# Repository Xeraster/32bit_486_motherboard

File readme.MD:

here are the schematics for the 32 bit 486 motherboard. This is the version where I fixed all the stuff that was wrong.

You will need the dual fpga chipset verilog code to run this. https://github.com/Xeraster/dual-ice40-fpga-486-chipset

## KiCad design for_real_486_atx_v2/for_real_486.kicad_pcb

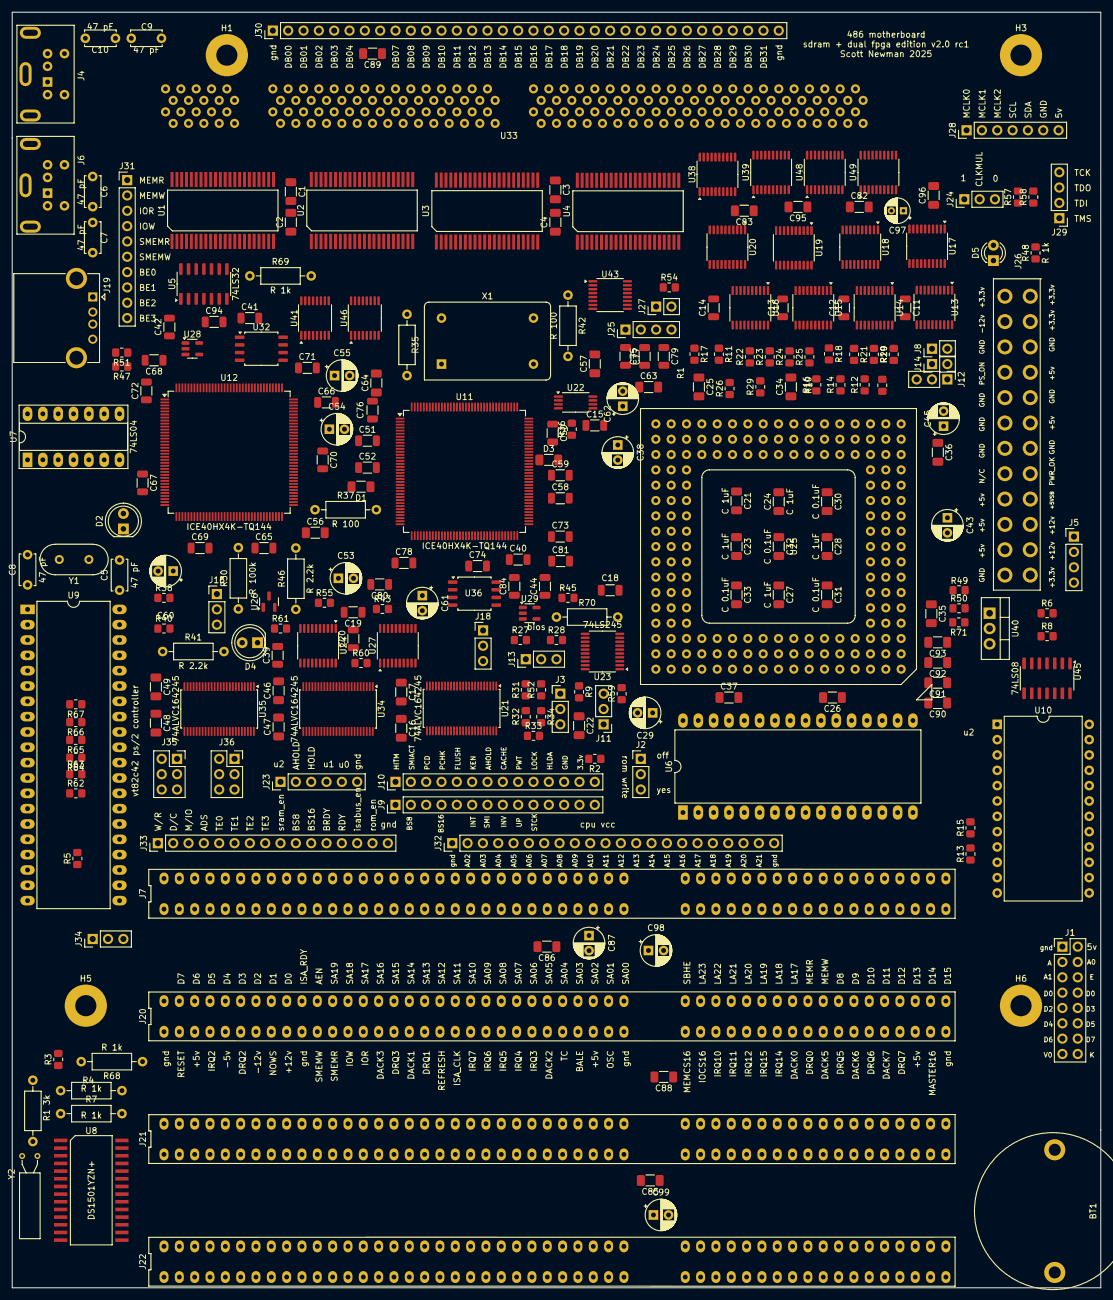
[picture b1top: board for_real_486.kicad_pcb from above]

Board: 4 copper layers, 180.3 x 211.3 mm, 256 parts (0 on the bottom side), 503 nets, no tracks yet.

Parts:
BT1: Battery_Cell; cr2032_holder
C1, C2, C3, C4, C30, C31, C32, C33, C34, C35, C36, C37, C56, C57, C64, C90, C92: C 0.1uF; C_1206_3216Metric_Pad1.33x1.80mm_HandSolder
C5, C6, C7, C8, C9, C10: 47 pF; C_Disc_D5.0mm_W2.5mm_P5.00mm
C11, C12, C13, C14, C18, C19, C20, C39, C40, C41, C42, C44, C65, C66, C69, C70, C73, C74, C77, C78, C81, C84, C94: C 0.1uF; C_1206_3216Metric
C15, C50: 0.1uF; C_1206_3216Metric
C16, C17, C46, C47, C48, C49, C82, C83, C85, C86, C95, C96: 0.1uF; C_1206_3216Metric_Pad1.33x1.80mm_HandSolder
C21, C22, C23, C24, C25, C26, C27, C28, C88, C89, C91, C93: C 1uF; C_1206_3216Metric_Pad1.33x1.80mm_HandSolder
C29, C38, C43, C45, C53, C54, C55, C60, C61, C62, C87, C98, C99: C_Polarized; CP_Radial_D5.0mm_P2.50mm
C51, C58: C 10uF; C_1206_3216Metric
C52, C59: SMD 0.1uF; C_1206_3216Metric
C63: C 0.1nF; C_1206_3216Metric_Pad1.33x1.80mm_HandSolder
C67, C68, C71, C72, C75, C76, C79, C80: C 1uF; C_1206_3216Metric
C97: C_Polarized; CP_Radial_D4.0mm_P2.00mm
D1, D3: D; C_1206_3216Metric_Pad1.33x1.80mm_HandSolder
D2, D4: LED; LED_D5.0mm
D5: LED; LED_D3.0mm
H1, H3, H5, H6: MountingHole; MountingHole_3.5mm_Pad
J1: Conn_02x08_Counter_Clockwise; PinHeader_2x08_P2.54mm_Vertical
J2, J3, J11, J12, J13, J16, J18, J24, J34: Conn_01x03; PinHeader_1x03_P2.54mm_Vertical
J4, J6: Mini-DIN-6; connector_mini6din
J5, J25, J29: Conn_01x04; PinHeader_1x04_P2.54mm_Vertical
J7, J20, J21, J22: Bus_ISA_16bit; DIP-98_ISA
J8, J14, J27: Conn_01x02; PinHeader_1x02_P2.54mm_Vertical
J9, J10: Conn_01x14; PinHeader_1x14_P2.54mm_Vertical
J19: USB_A; USB_A_CONNFLY_DS1095-WNR0
J23: Conn_01x06; PinHeader_1x06_P2.54mm_Vertical
J26: ATX-24; 24pinATX_newer
J28: Conn_01x07; PinHeader_1x07_P2.54mm_Vertical
J30: Conn_01x34; PinHeader_1x34_P2.54mm_Vertical
J31: Conn_01x10; PinHeader_1x10_P2.54mm_Vertical
J32: Conn_01x22; PinHeader_1x22_P2.54mm_Vertical
J33: Conn_01x16; PinHeader_1x16_P2.54mm_Vertical
J35, J36: Conn_01x06; PinSocket_2x03_P2.54mm_Vertical
R1: 3k; R_Axial_DIN0207_L6.3mm_D2.5mm_P10.16mm_Horizontal
R2, R3, R5, R9, R10, R11, R12, R14, R16, R26, R29, R31, R32, R33, R34, R38, R40, R43, R45, R52, R55, R57, R58, R59, R60, R61, R62, R63, R64, R65, R66, R67: R 10k; R_0805_2012Metric_Pad1.20x1.40mm_HandSolder
R4, R7, R35, R68, R69, R70: R 1k; R_Axial_DIN0207_L6.3mm_D2.5mm_P10.16mm_Horizontal
R6, R8, R48, R54: R 1k; R_0805_2012Metric_Pad1.20x1.40mm_HandSolder
R13, R15, R18, R19, R20, R21, R22, R23, R24, R25, R27, R28: 10k; R_0805_2012Metric_Pad1.20x1.40mm_HandSolder
R17: R 10K; R_0805_2012Metric_Pad1.20x1.40mm_HandSolder
R30: R 100k; R_Axial_DIN0207_L6.3mm_D2.5mm_P10.16mm_Horizontal
R36, R49, R50, R71: R; R_0805_2012Metric_Pad1.20x1.40mm_HandSolder
R37, R42: R 100; R_Axial_DIN0207_L6.3mm_D2.5mm_P10.16mm_Horizontal
R41, R46: R 2.2k; R_Axial_DIN0207_L6.3mm_D2.5mm_P10.16mm_Horizontal
R47, R51: R 33; R_0805_2012Metric_Pad1.20x1.40mm_HandSolder
U1, U2, U3, U4: CY7C1049G30; TSOP-44
U5: 74LS32; SO-14_3.9x8.65mm_P1.27mm
U6: 29F010-PDIP; DIP-32_W15.24mm_LongPads
U7: 74LS04; DIP-14_W7.62mm_Socket_LongPads
U8: DS1501YZN+; SOIC-BQ4845
U9: HT6542B; DIP-40_W15.24mm_LongPads
U10: 8254; DIP-24_W15.24mm
U11, U12: ICE40HX4K-TQ144; TQFP-144_20x20mm_P0.5mm
U13, U14, U15, U16, U17, U18, U19, U20, U23, U24, U27: 74LS245; TSSOP-20_4.4x6.5mm_P0.65mm
U21, U34, U35: 74ALVC164245; TSSOP-48_6.1x12.5mm_P0.5mm
U22: LMK1C1103PWR; TSSOP-8_4.4x3mm_P0.65mm
U25: i486SX; PGA168
U26: LM809; SOT-23
U28, U29: AP7347DQ; SOT-23-5
U32, U36: SOIC-8_5.275x5.275mm_P1.27mm
U33: SDRAM_socket
U38, U39, U48, U49: 74LS373; TSSOP-20_4.4x6.5mm_P0.65mm
U40: LM317_TO-220; TO-220-3_Vertical
U41, U43, U46: 74LS165; TSSOP-16_4.4x5mm_P0.65mm
U45: 74LS08; SO-14_3.9x8.65mm_P1.27mm
X1: ACO-xxxMHz-A; Oscillator_DIP-14
Y1: Crystal; Crystal_HC18-U_Vertical
Y2: Crystal; Crystal_AT310_D3.0mm_L10.0mm_Horizontal

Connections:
+1V2: C44.1, C53.1, C54.1, C60.1, C61.1, C69.1, C70.1, C71.1, C72.1, C77.1, C78.1, C79.1, C80.1, C94.1, R37.1, R42.1, U11.27 (VCC), U11.40 (VCC), U11.92 (VCC), U11.111 (VCC), U12.27 (VCC), U12.40 (VCC), U12.92 (VCC), U12.111 (VCC), U28.5 (V_out), U29.5 (V_out)
+3.3V: C1.1, C2.1, C3.1, C4.1, C11.2, C12.1, C13.1, C14.1, C15.2, C17.1, C18.2, C19.1, C20.1, C39.1, C40.1, C41.1, C42.1, C43.1, C47.1, C49.1, C50.1, C55.1, C56.2, C57.2, C62.1, C63.2, C64.2, C65.1, C66.1, C67.1, C68.1, C73.1, C74.1, C75.1, C76.1, C82.1, C83.1, C84.1, C85.1, C86.1, C87.1, C88.1, C89.1, C95.1, C96.1, C97.1, D1.2 (A), D3.2 (A), J10.13, J26.1 (+3.3V), J26.2 (+3.3V), J26.12 (+3.3V), J26.13 (+3.3V), J35.6, J36.6, R10.1, R12.1, R14.1, R16.1, R19.2, R20.1, R21.1, R36.2, R38.1, R40.2, R43.1, R45.2, R55.1, R59.1, R60.1, R61.1, R69.2, R70.2, U1.11 (VCC), U1.33 (VCC), U2.11 (VCC), U2.33 (VCC), U3.11 (VCC), U3.33 (VCC), U4.11 (VCC), U4.33 (VCC), U5.14 (VCC), U11.6 (VCCIO_3), U11.30 (VCCIO_3), U11.46 (VCCIO_2), U11.57 (VCCIO_2), U11.72 (VCC_SPI), U11.89 (VCCIO_1), U11.100 (VCCIO_1), U11.123 (VCCIO_0), U11.131 (VCCIO_0), U12.6 (VCCIO_3), U12.30 (VCCIO_3), U12.46 (VCCIO_2), U12.57 (VCCIO_2), U12.72 (VCC_SPI), U12.89 (VCCIO_1), U12.100 (VCCIO_1), U12.123 (VCCIO_0), U12.131 (VCCIO_0), U13.20 (VCC), U14.20 (VCC), U15.20 (VCC), U16.20 (VCC), U17.20 (VCC), U18.20 (VCC), U19.20 (VCC), U20.20 (VCC), U21.31 (V_{CC(A)}), U21.42 (V_{CC(A)}), U22.6 (VDD), U23.20 (VCC), U24.20 (VCC), U26.3 (VCC), U27.20 (VCC), U28.1 (V_in), U29.1 (V_in), U32.8 (VCC), U33.6 (Vcc), U33.18 (Vcc), U33.26 (Vcc), U33.40 (Vcc), U33.41 (Vcc), U33.49 (Vcc), U33.59 (Vcc), U33.73 (Vcc), U33.84 (Vcc), U33.90 (Vcc), U33.102 (Vcc), U33.110 (Vcc), U33.124 (Vcc), U33.133 (Vcc), U33.143 (Vcc), U33.157 (Vcc), U33.168 (Vcc), U34.31 (V_{CC(A)}), U34.42 (V_{CC(A)}), U35.31 (V_{CC(A)}), U35.42 (V_{CC(A)}), U36.8 (VCC), U38.20 (VCC), U39.20 (VCC), U41.16 (VCC), U43.16 (VCC), U45.14 (VCC), U46.16 (VCC), U48.20 (VCC), U49.20 (VCC), X1.14 (Vcc)
+5V: C16.2, C45.1, C46.2, C48.2, C98.1, C99.1, J1.2, J1.3, J4.4, J6.4, J7.3 (+5V), J7.29 (VCC), J7.78 (+5V), J8.1, J12.1, J19.1 (VBUS), J20.3 (+5V), J20.29 (VCC), J20.78 (+5V), J21.3 (+5V), J21.29 (VCC), J21.78 (+5V), J22.3 (+5V), J22.29 (VCC), J22.78 (+5V), J26.4 (+5V), J26.6 (+5V), J26.21 (+5V), J26.22 (+5V), J26.23 (+5V), J27.2, J28.7, R2.1, R3.1, R4.1, R5.2, R6.2, R7.2, R8.2, U6.32 (VCC), U7.14 (VCC), U8.28 (Vcc), U9.26 (TEST), U9.40 (Vdd), U10.24 (VCC), U21.7 (V_{CC(B)}), U21.18 (V_{CC(B)}), U34.7 (V_{CC(B)}), U34.18 (V_{CC(B)}), U35.7 (V_{CC(B)}), U35.18 (V_{CC(B)})
+12V: C90.1, C91.1, J7.9 (+12V), J20.9 (+12V), J21.9 (+12V), J22.9 (+12V), J26.10 (+12V), J26.11 (+12V), U40.3 (VI)
A00: U11.41 (IOB_63), U13.2 (A0)
A01: U11.42 (IOB_64), U13.3 (A1)
A02: U13.4 (A2), U25.Q14 (A2)
A03: U13.5 (A3), U25.R15 (A3)
A04: U13.6 (A4), U25.S16 (A4)
A05: U13.7 (A5), U25.Q12 (A5)
A06: U13.8 (A6), U25.S15 (A6)
A07: U13.9 (A7), U25.Q13 (A7)
A08: U14.2 (A0), U25.R13 (A8)
A09: U14.3 (A1), U25.Q11 (A9)
A10: U14.4 (A2), U25.S13 (A10)
A11: U14.5 (A3), U25.R12 (A11)
A12: U14.6 (A4), U25.S7 (A12)
A13: U14.7 (A5), U25.Q10 (A13)
A14: U14.8 (A6), U25.S5 (A14)
A15: U14.9 (A7), U25.R7 (A15)
A16: U15.2 (A0), U25.Q9 (A16)
A17: U15.3 (A1), U25.Q3 (A17)
A18: U15.4 (A2), U25.R5 (A18)
A19: U15.5 (A3), U25.Q4 (A19)
A20: U15.6 (A4), U25.Q8 (A20)
A20M: J3.1, U25.D15 (A20M)
A21: U15.7 (A5), U25.Q5 (A21)
A22: U15.8 (A6), U25.Q7 (A22)
A23: U15.9 (A7), U25.S3 (A23)
A24: U16.2 (A0), U25.Q6 (A24)
A25: U16.3 (A1), U25.R2 (A25)
A26: U16.4 (A2), U25.S2 (A26)
A27: U16.5 (A3), U25.S1 (A27)
A28: U16.6 (A4), U25.R1 (A28)
A29: U16.7 (A5), U25.P2 (A29)
A30: U16.8 (A6), U25.P3 (A30)
A31: U16.9 (A7), U25.Q1 (A31)
AB00: J1.4, U6.12 (A0), U8.10 (A0), U10.19 (A0), U12.49 (IOB_81_GBIN5), U13.18 (B0), U21.2 (1B0)
AB01: J1.5, U1.3 (A0), U2.3 (A0), U3.3 (A0), U4.3 (A0), U6.11 (A1), U8.9 (A1), U10.20 (A1), U12.44 (IOB_72), U13.17 (B1), U21.3 (1B1)
AB02: J32.2, U1.4 (A1), U2.4 (A1), U3.4 (A1), U4.4 (A1), U6.10 (A2), U8.8 (A2), U9.9 (A0), U11.73 (IOR_109), U12.45 (IOB_73), U13.16 (B2), U21.5 (1B2)
AB03: J32.3, U1.5 (A2), U2.5 (A2), U3.5 (A2), U4.5 (A2), U6.9 (A3), U8.7 (A3), U11.74 (IOR_110), U13.15 (B3), U21.6 (1B3)
AB04: J32.4, U1.6 (A3), U2.6 (A3), U3.6 (A3), U4.6 (A3), U6.8 (A4), U8.6 (A4), U11.75 (IOR_111), U13.14 (B4), U21.8 (1B4)
AB05: J32.5, U1.7 (A4), U2.7 (A4), U3.7 (A4), U4.7 (A4), U6.7 (A5), U11.76 (IOR_112), U13.13 (B5), U21.9 (1B5)
AB06: J32.6, U1.16 (A5), U2.16 (A5), U3.16 (A5), U4.16 (A5), U6.6 (A6), U11.78 (IOR_114), U13.12 (B6), U21.11 (1B6)
AB07: J32.7, U1.17 (A6), U2.17 (A6), U3.17 (A6), U4.17 (A6), U6.5 (A7), U11.79 (IOR_115), U13.11 (B7), U21.12 (1B7)
AB08: J32.8, U1.18 (A7), U2.18 (A7), U3.18 (A7), U4.18 (A7), U6.27 (A8), U11.80 (IOR_116), U14.18 (B0), U21.13 (2B0)
AB09: J32.9, U1.19 (A8), U2.19 (A8), U3.19 (A8), U4.19 (A8), U6.26 (A9), U11.81 (IOR_117), U14.17 (B1), U21.14 (2B1)
AB10: J32.10, U1.20 (A9), U2.20 (A9), U3.20 (A9), U4.20 (A9), U6.23 (A10), U11.82 (IOR_118), U14.16 (B2), U21.16 (2B2)
AB11: J32.11, U1.26 (A10), U2.26 (A10), U3.26 (A10), U4.26 (A10), U6.25 (A11), U11.83 (IOR_119), U14.15 (B3), U21.17 (2B3)
AB12: J32.12, U1.27 (A11), U2.27 (A11), U3.27 (A11), U4.27 (A11), U6.4 (A12), U11.84 (IOR_120), U14.14 (B4), U21.19 (2B4)
AB13: J32.13, U1.28 (A12), U2.28 (A12), U3.28 (A12), U4.28 (A12), U6.28 (A13), U11.85 (IOR_128), U14.13 (B5), U21.20 (2B5)
AB14: J32.14, U1.29 (A13), U2.29 (A13), U3.29 (A13), U4.29 (A13), U6.29 (A14), U11.87 (IOR_136), U14.12 (B6), U21.22 (2B6)
AB15: J32.15, U1.30 (A14), U2.30 (A14), U3.30 (A14), U4.30 (A14), U6.3 (A15), U11.88 (IOR_137), U14.11 (B7), U21.23 (2B7)
AB16: J32.16, U1.38 (A15), U2.38 (A15), U3.38 (A15), U4.38 (A15), U6.2 (A16), U11.90 (IOR_138), U15.18 (B0), U35.2 (1B0)
AB17: J32.17, U1.39 (A16), U2.39 (A16), U3.39 (A16), U4.39 (A16), U11.91 (IOR_139), U15.17 (B1), U35.3 (1B1)
AB18: J32.18, U1.40 (A17), U2.40 (A17), U3.40 (A17), U4.40 (A17), U11.94 (IOR_141_GBIN2), U15.16 (B2), U35.5 (1B2)
AB19: J32.19, U1.41 (A18), U2.41 (A18), U3.41 (A18), U4.41 (A18), U11.95 (IOR_144), U15.15 (B3), U35.6 (1B3)
AB20: J32.20, U11.96 (IOR_146), U15.14 (B4), U35.8 (1B4)
AB21: J32.21, U11.97 (IOR_147), U15.13 (B5), U35.9 (1B5)
AB22: U11.98 (IOR_148), U15.12 (B6), U35.11 (1B6)
AB23: U11.99 (IOR_152), U15.11 (B7), U35.12 (1B7)
AB24: U11.101 (IOR_160), U16.18 (B0), U35.13 (2B0)
AB25: U11.102 (IOR_161), U16.17 (B1), U35.14 (2B1)
AB26: U11.104 (IOR_164), U16.16 (B2), U35.16 (2B2)
AB27: U11.105 (IOR_165), U16.15 (B3), U35.17 (2B3)
AB28: U11.106 (IOR_166), U16.14 (B4), U35.19 (2B4)
AB29: U11.144 (IOT_222), U16.13 (B5), U35.20 (2B5)
AB30: U11.143 (IOT_221), U16.12 (B6), U35.22 (2B6)
AB31: U11.142 (IOT_220), U16.11 (B7), U35.23 (2B7)
ADS: J33.4, U23.9 (A7), U25.S17 (ADS)
ADT_EN: U11.107 (IOR_167), U12.110 (IOT_168), U13.19 (CE), U14.19 (CE), U15.19 (CE), U16.19 (CE)
AEN: J7.42 (AEN), J20.42 (AEN), J21.42 (AEN), J22.42 (AEN)
AHOLD: J10.7, J23.2, U25.A17 (AHOLD)
AP_INC: U11.61 (IOB_96), U43.13 (D2)
BA0: U12.39 (IOB_61), U33.122 (BA0)
BA1: U12.41 (IOB_63), U33.39 (BA1)
BALE: J7.28 (ALE), J20.28 (ALE), J21.28 (ALE), J22.28 (ALE), U7.12
BCLK0: U22.3 (Y0), U25.C3 (CLK)
BCLK1: U22.8 (Y1), U41.2 (CP), U43.2 (CP), U46.2 (CP)
BE0: J31.7, U5.13, U23.2 (A0), U25.K15 (BE0)
BE1: J31.8, U5.10, U23.3 (A1), U25.J16 (BE1)
BE2: J31.9, U5.5, U23.4 (A2), U25.J15 (BE2)
BE3: J31.10, U5.2, U23.5 (A3), U25.F17 (BE3)
BLAST: U25.R16 (BLAST), U27.3 (A1)
BOFF: R19.1, U25.D17 (BOFF)
BRDY: J33.12, U11.21 (IOL_14A_GBIN6), U25.H15 (BRDY)
BREQ: U25.Q15 (BREQ), U27.2 (A0)
BS8: J9.2, J33.10, U11.19 (IOL_13A), U12.3 (IOL_3A), U25.D16 (BS8)
BS16: J9.4, J33.11, U11.20 (IOL_13B_GBIN7), U12.4 (IOL_3B), U25.C17 (BS16)
CACHE: J10.8, U25.B12 (CACHE)
CDONE_PROG: D4.2 (A), U11.65 (CDONE)
CDONE_PROG2: D2.2 (A), U12.65 (CDONE)
CH_RDY: J7.41 (IO_READY), J20.41 (IO_READY), J21.41 (IO_READY), J22.41 (IO_READY), U27.7 (A5)
CK0: U11.37 (IOB_56), U12.93 (IOR_140_GBIN3), U33.42 (CK0)
CK2: U12.94 (IOR_141_GBIN2), U33.79 (CK2)
CRAP_SHIFT: U12.78 (IOR_114), U41.9 (Q7)
CRESET: J18.2, U11.66 (~CRESET)
CRESET2: J16.2, U12.66 (~CRESET)
D00: U17.2 (A0), U25.P1 (D0)
D01: U17.3 (A1), U25.N2 (D1)
D02: U17.4 (A2), U25.N1 (D2)
D03: U17.5 (A3), U25.H2 (D3)
D04: U17.6 (A4), U25.M3 (D4)
D05: U17.7 (A5), U25.J2 (D5)
D06: U17.8 (A6), U25.L2 (D6)
D07: U17.9 (A7), U25.L3 (D7)
D08: U18.2 (A0), U25.F2 (D8)
D09: U18.3 (A1), U25.D1 (D9)
D10: U18.4 (A2), U25.E3 (D10)
D11: U18.5 (A3), U25.C1 (D11)
D12: U18.6 (A4), U25.G3 (D12)
D13: U18.7 (A5), U25.D2 (D13)
D14: U18.8 (A6), U25.K3 (D14)
D15: U18.9 (A7), U25.F3 (D15)
D16: U19.2 (A0), U25.J3 (D16)
D17: U19.3 (A1), U25.D3 (D17)
D18: U19.4 (A2), U25.C2 (D18)
D19: U19.5 (A3), U25.B1 (D19)
D20: U19.6 (A4), U25.A1 (D20)
D21: U19.7 (A5), U25.B2 (D21)
D22: U19.8 (A6), U25.A2 (D22)
D23: U19.9 (A7), U25.A4 (D23)
D24: U20.2 (A0), U25.A6 (D24)
D25: U20.3 (A1), U25.B6 (D25)
D26: U20.4 (A2), U25.C7 (D26)
D27: U20.5 (A3), U25.C6 (D27)
D28: U20.6 (A4), U25.C8 (D28)
D29: U20.7 (A5), U25.A8 (D29)
D30: U20.8 (A6), U25.C9 (D30)
D31: U20.9 (A7), U25.B8 (D31)
DACK0: J7.70 (~DACK0), J20.70 (~DACK0), J21.70 (~DACK0), J22.70 (~DACK0)
DACK1: J7.17 (~DACK1), J20.17 (~DACK1), J21.17 (~DACK1), J22.17 (~DACK1)
DACK2: J7.26 (~DACK2), J20.26 (~DACK2), J21.26 (~DACK2), J22.26 (~DACK2)
DACK3: J7.15 (~DACK3), J20.15 (~DACK3), J21.15 (~DACK3), J22.15 (~DACK3)
DACK5: J7.72 (~DACK5), J20.72 (~DACK5), J21.72 (~DACK5), J22.72 (~DACK5)
DACK6: J7.74 (~DACK6), J20.74 (~DACK6), J21.74 (~DACK6), J22.74 (~DACK6)
DACK7: J7.76 (~DACK7), J20.76 (~DACK7), J21.76 (~DACK7), J22.76 (~DACK7)
DB00: J30.2, U1.9 (D0), U12.107 (IOR_167), U17.18 (B0), U33.2 (DQ0), U49.3 (D0)
DB01: J30.3, U1.10 (D1), U12.106 (IOR_166), U17.17 (B1), U33.3 (DQ1), U49.4 (D1)
DB02: J30.4, U1.13 (D2), U12.105 (IOR_165), U17.16 (B2), U33.4 (DQ2), U49.7 (D2)
DB03: J30.5, U1.14 (D3), U12.104 (IOR_164), U17.15 (B3), U33.5 (DQ3), U49.8 (D3)
DB04: J30.6, U1.31 (D4), U12.102 (IOR_161), U17.14 (B4), U33.7 (DQ4), U49.13 (D4)
DB05: J30.7, U1.32 (D5), U12.101 (IOR_160), U17.13 (B5), U33.8 (DQ5), U49.14 (D5)
DB06: J30.8, U1.35 (D6), U12.99 (IOR_152), U17.12 (B6), U33.9 (DQ6), U49.17 (D6)
DB07: J30.9, U1.36 (D7), U12.98 (IOR_148), U17.11 (B7), U33.10 (DQ7), U49.18 (D7)
DB08: J30.10, U2.9 (D0), U12.144 (IOT_222), U18.18 (B0), U33.11 (DQ8), U48.3 (D0)
DB09: J30.11, U2.10 (D1), U12.143 (IOT_221), U18.17 (B1), U33.13 (DQ9), U48.4 (D1)
DB10: J30.12, U2.13 (D2), U12.142 (IOT_220), U18.16 (B2), U33.14 (DQ10), U48.7 (D2)
DB11: J30.13, U2.14 (D3), U12.141 (IOT_219), U18.15 (B3), U33.15 (DQ11), U48.8 (D3)
DB12: J30.14, U2.31 (D4), U12.139 (IOT_217), U18.14 (B4), U33.16 (DQ12), U48.13 (D4)
DB13: J30.15, U2.32 (D5), U12.138 (IOT_216), U18.13 (B5), U33.17 (DQ13), U48.14 (D5)
DB14: J30.16, U2.35 (D6), U12.137 (IOT_215), U18.12 (B6), U33.19 (DQ14), U48.17 (D6)
DB15: J30.17, U2.36 (D7), U12.136 (IOT_214), U18.11 (B7), U33.20 (DQ15), U48.18 (D7)
DB16: J30.18, U3.9 (D0), U12.135 (IOT_213), U19.18 (B0), U33.55 (DQ16), U39.3 (D0)
DB17: J30.19, U3.10 (D1), U12.134 (IOT_212), U19.17 (B1), U33.56 (DQ17), U39.4 (D1)
DB18: J30.20, U3.13 (D2), U12.128 (IOT_197_GBIN1), U19.16 (B2), U33.57 (DQ18), U39.7 (D2)
DB19: J30.21, U3.14 (D3), U12.125 (IOT_192), U19.15 (B3), U33.58 (DQ19), U39.8 (D3)
DB20: J30.22, U3.31 (D4), U12.124 (IOT_191), U19.14 (B4), U33.60 (DQ20), U39.13 (D4)
DB21: J30.23, U3.32 (D5), U12.122 (IOT_190), U19.13 (B5), U33.65 (DQ21), U39.14 (D5)
DB22: J30.24, U3.35 (D6), U12.121 (IOT_181), U19.12 (B6), U33.66 (DQ22), U39.17 (D6)
DB23: J30.25, U3.36 (D7), U12.120 (IOT_179), U19.11 (B7), U33.67 (DQ23), U39.18 (D7)
DB24: J30.26, U4.9 (D0), U12.119 (IOT_178), U20.18 (B0), U33.69 (DQ24), U38.3 (D0)
DB25: J30.27, U4.10 (D1), U12.118 (IOT_177), U20.17 (B1), U33.70 (DQ25), U38.4 (D1)
DB26: J30.28, U4.13 (D2), U12.117 (IOT_174), U20.16 (B2), U33.71 (DQ26), U38.7 (D2)
DB27: J30.29, U4.14 (D3), U12.116 (IOT_173), U20.15 (B3), U33.72 (DQ27), U38.8 (D3)
DB28: J30.30, U4.31 (D4), U12.115 (IOT_172), U20.14 (B4), U33.74 (DQ28), U38.13 (D4)
DB29: J30.31, U4.32 (D5), U12.114 (IOT_171), U20.13 (B5), U33.75 (DQ29), U38.14 (D5)
DB30: J30.32, U4.35 (D6), U12.113 (IOT_170), U20.12 (B6), U33.76 (DQ30), U38.17 (D6)
DB31: J30.33, U4.36 (D7), U12.112 (IOT_169), U20.11 (B7), U33.77 (DQ31), U38.18 (D7)
DB32: U33.86 (DQ32), U49.2 (O0)
DB33: U33.87 (DQ33), U49.5 (O1)
DB34: U33.88 (DQ34), U49.6 (O2)
DB35: U33.89 (DQ35), U49.9 (O3)
DB36: U33.91 (DQ36), U49.12 (O4)
DB37: U33.92 (DQ37), U49.15 (O5)
DB38: U33.93 (DQ38), U49.16 (O6)
DB39: U33.94 (DQ39), U49.19 (O7)
DB40: U33.95 (DQ40), U48.2 (O0)
DB41: U33.97 (DQ41), U48.5 (O1)
DB42: U33.98 (DQ42), U48.6 (O2)
DB43: U33.99 (DQ43), U48.9 (O3)
DB44: U33.100 (DQ44), U48.12 (O4)
DB45: U33.101 (DQ45), U48.15 (O5)
DB46: U33.103 (DQ46), U48.16 (O6)
DB47: U33.104 (DQ47), U48.19 (O7)
DB48: U33.139 (DQ48), U39.2 (O0)
DB49: U33.140 (DQ49), U39.5 (O1)
DB50: U33.141 (DQ50), U39.6 (O2)
DB51: U33.142 (DQ51), U39.9 (O3)
DB52: U33.144 (DQ52), U39.12 (O4)
DB53: U33.149 (DQ53), U39.15 (O5)
DB54: U33.150 (DQ54), U39.16 (O6)
DB55: U33.151 (DQ55), U39.19 (O7)
DB56: U33.153 (DQ56), U38.2 (O0)
DB57: U33.154 (DQ57), U38.5 (O1)
DB58: U33.155 (DQ58), U38.6 (O2)
DB59: U33.156 (DQ59), U38.9 (O3)
DB60: U33.158 (DQ60), U38.12 (O4)
DB61: U33.159 (DQ61), U38.15 (O5)
DB62: U33.160 (DQ62), U38.16 (O6)
DB63: U33.161 (DQ63), U38.19 (O7)
DQMB0: U12.82 (IOR_118), U33.28 (DQM0)
DQMB1: U12.83 (IOR_119), U33.29 (DQM1)
DQMB2: U12.84 (IOR_120), U33.46 (DQM2)
DQMB3: U12.85 (IOR_128), U33.47 (DQM3)
DQMB_HIGH: U12.87 (IOR_136), U33.112 (DQM4), U33.113 (DQM5), U33.130 (DQM6), U33.131 (DQM7)
DRQ0: J7.71 (DRQ0), J20.71 (DRQ0), J21.71 (DRQ0), J22.71 (DRQ0)
DRQ1: J7.18 (DRQ1), J20.18 (DRQ1), J21.18 (DRQ1), J22.18 (DRQ1), U46.12 (D1)
DRQ2: J7.6 (DRQ2), J20.6 (DRQ2), J21.6 (DRQ2), J22.6 (DRQ2), U46.13 (D2)
DRQ3: J7.16 (DRQ3), J20.16 (DRQ3), J21.16 (DRQ3), J22.16 (DRQ3), U46.14 (D3)
DRQ5: J7.73 (DRQ5), J20.73 (DRQ5), J21.73 (DRQ5), J22.73 (DRQ5), U46.4 (D5)
DRQ6: J7.75 (DRQ6), J20.75 (DRQ6), J21.75 (DRQ6), J22.75 (DRQ6), U46.5 (D6)
DRQ7: J7.77 (DRQ7), J20.77 (DRQ7), J21.77 (DRQ7), J22.77 (DRQ7), U46.6 (D7)
D/C: J33.2, U23.7 (A5), U25.M15 (D/C)
EADS: R20.2, U25.B17 (EADS)
FLUSH: J10.5, U25.C15 (FLUSH)
FPGA_ADS: U7.13, U11.114 (IOT_171), U12.74 (IOR_110), U23.11 (B7)
FPGA_BE0: U11.115 (IOT_172), U23.18 (B0)
FPGA_BE1: U11.116 (IOT_173), U23.17 (B1)
FPGA_BE2: U11.117 (IOT_174), U23.16 (B2)
FPGA_BE3: U11.118 (IOT_177), U23.15 (B3)
FPGA_CH_RDY: U12.8 (IOL_4B), U27.13 (B5)
FPGA_CLOCK: U11.93 (IOR_140_GBIN3), U12.130 (IOT_206), U22.5 (Y2)
FPGA_D/C: U11.112 (IOT_169), U12.63 (IOB_103_CBSEL0), U23.13 (B5)
FPGA_IOCS16: U12.1 (IOL_2A), U27.11 (B7)
FPGA_IOR: J31.3, U11.25 (IOL_18A), U24.4 (A2)
FPGA_IOW: J31.4, U11.26 (IOL_18B), U24.5 (A3)
FPGA_MEMCS16: U12.2 (IOL_2B), U27.12 (B6)
FPGA_MEMR: J31.1, U11.31 (IOL_24A), U24.2 (A0)
FPGA_MEMW: J31.2, U11.32 (IOL_24B), U24.3 (A1)
FPGA_M/IO: U11.113 (IOT_170), U12.64 (IOB_104_CBSEL1), U23.12 (B6)
FPGA_NOWS: U12.7 (IOL_4A), U27.14 (B4)
FPGA_RESET: J16.3, J18.3, R30.1, U26.2 (~RESET)
FPGA_RESET_BUTTON: J25.3, R55.2, U11.52 (IOB_82_GBIN4)
FPGA_SMEMR: J31.5, U11.28 (IOL_23A), U24.6 (A4)
FPGA_SMEMW: J31.6, U11.29 (IOL_23B), U24.7 (A5)
FPGA_W/R: U11.110 (IOT_168), U12.62 (IOB_102), U23.14 (B4)
GND: BT1.2 (-), C1.2, C2.2, C3.2, C4.2, C5.1, C6.1, C7.1, C8.1, C9.1, C10.1, C11.1, C12.2, C13.2, C14.2, C15.1, C16.1, C17.2, C18.1, C19.2, C20.2, C21.1, C22.1, C23.1, C24.1, C25.1, C26.1, C27.1, C28.1, C29.2, C30.2, C31.2, C32.2, C33.2, C34.2, C35.2, C36.2, C37.2, C38.2, C39.2, C40.2, C41.2, C42.2, C43.2, C44.2, C45.2, C46.1, C47.2, C48.1, C49.2, C50.2, C53.2, C54.2, C55.2, C56.1, C57.1, C60.2, C61.2, C62.2, C63.1, C64.1, C65.2, C66.2, C67.2, C68.2, C69.2, C70.2, C71.2, C72.2, C73.2, C74.2, C75.2, C76.2, C77.2, C78.2, C79.2, C80.2, C82.2, C83.2, C84.2, C85.2, C86.2, C87.2, C88.2, C89.2, C90.2, C91.2, C92.2, C93.2, C94.2, C95.2, C96.2, C97.2, C98.2, C99.2, J1.1, J1.16, J4.3, J5.1, J6.3, J7.1 (GND), J7.10 (GND), J7.31 (GND), J7.80 (GND), J9.1, J10.12, J16.1, J18.1, J19.4 (GND), J20.1 (GND), J20.10 (GND), J20.31 (GND), J20.80 (GND), J21.1 (GND), J21.10 (GND), J21.31 (GND), J21.80 (GND), J22.1 (GND), J22.10 (GND), J22.31 (GND), J22.80 (GND), J23.6, J25.1, J25.4, J26.3 (GND), J26.5 (GND), J26.7 (GND), J26.15 (GND), J26.17 (GND), J26.18 (GND), J26.19 (GND), J26.24 (GND), J28.6, J30.1, J30.34, J32.1, J32.22, J33.16, J35.5, J36.5, R1.2, R9.1, R11.1, R13.2, R15.2, R17.1, R18.1, R26.2, R27.1, R29.2, R30.2, R31.1, R32.1, R33.1, R34.1, R35.1, R41.2, R46.2, R48.2, R52.1, R54.2, R58.1, R62.1, R63.1, R64.2, R65.2, R66.2, R67.2, R68.2, R71.2, U1.12 (VSS), U1.34 (VSS), U2.12 (VSS), U2.34 (VSS), U3.12 (VSS), U3.34 (VSS), U4.12 (VSS), U4.34 (VSS), U5.7 (GND), U6.16 (GND), U7.7 (GND), U8.14 (Vss), U8.21 (Vss), U9.20 (Vss), U10.12 (GND), U11.5 (GND), U11.13 (GND), U11.14 (GND), U11.59 (GND), U11.69 (GND), U11.86 (GND), U11.103 (GND), U11.132 (GND), U11.140 (GND), U12.5 (GND), U12.13 (GND), U12.14 (GND), U12.59 (GND), U12.69 (GND), U12.86 (GND), U12.103 (GND), U12.132 (GND), U12.140 (GND), U13.10 (GND), U14.10 (GND), U15.10 (GND), U16.10 (GND), U17.10 (GND), U18.10 (GND), U19.10 (GND), U20.10 (GND), U21.4 (GND), U21.10 (GND), U21.15 (GND), U21.21 (GND), U21.28 (GND), U21.34 (GND), U21.39 (GND), U21.45 (GND), U22.4 (GND), U23.10 (GND), U24.10 (GND), U25.A7 (Vss), U25.A9 (Vss), U25.A11 (Vss), U25.B3 (Vss), U25.B4 (Vss), U25.B5 (Vss), U25.E1 (Vss), U25.E17 (Vss), U25.G1 (Vss), U25.G17 (Vss), U25.H1 (Vss), U25.H17 (Vss), U25.K1 (Vss), U25.K17 (Vss), U25.L1 (Vss), U25.L17 (Vss), U25.M1 (Vss), U25.M17 (Vss), U25.P17 (Vss), U25.Q2 (Vss), U25.R4 (Vss), U25.S6 (Vss), U25.S8 (Vss), U25.S9 (Vss), U25.S10 (Vss), U25.S11 (Vss), U25.S12 (Vss), U25.S14 (Vss), U26.1 (GND), U27.10 (GND), U28.2 (GND), U29.2 (GND), U32.4 (GND), U33.1 (Gnd), U33.12 (Gnd), U33.23 (Gnd), U33.32 (Gnd), U33.43 (Gnd), U33.54 (Gnd), U33.64 (Gnd), U33.68 (Gnd), U33.78 (Gnd), U33.85 (Gnd), U33.96 (Gnd), U33.107 (Gnd), U33.116 (Gnd), U33.127 (Gnd), U33.138 (Gnd), U33.148 (Gnd), U33.152 (Gnd), U33.162 (Gnd), U34.4 (GND), U34.10 (GND), U34.15 (GND), U34.21 (GND), U34.28 (GND), U34.34 (GND), U34.39 (GND), U34.45 (GND), U35.4 (GND), U35.10 (GND), U35.15 (GND), U35.21 (GND), U35.28 (GND), U35.34 (GND), U35.39 (GND), U35.45 (GND), U36.4 (GND), U38.10 (GND), U39.10 (GND), U41.8 (GND), U43.8 (GND), U45.7 (GND), U46.8 (GND), U48.10 (GND), U49.10 (GND), X1.7 (GND)
HITM: J10.1, U25.A12 (HITM)
HLDA: J10.11, U25.P15 (HLDA), U27.5 (A3)
HOLD: J23.3, R18.2, U25.E15 (HOLD)
INC: J9.7, U25.A13 (INC)
INT: J9.6, U12.81 (IOR_117), U25.A16 (INTR)
INTA: U11.34 (IOL_25B), U12.80 (IOR_116)
INV: J9.8, U25.A10 (INV)
IOCS16: J7.64 (~IOCS16), J20.64 (~IOCS16), J21.64 (~IOCS16), J22.64 (~IOCS16), U27.9 (A7)
IOR: J7.14 (~IOR), J20.14 (~IOR), J21.14 (~IOR), J22.14 (~IOR), U8.22 (~OE), U9.8 (~RD), U10.22 (~RD), U24.16 (B2)
IOW: J7.13 (~IOW), J20.13 (~IOW), J21.13 (~IOW), J22.13 (~IOW), U8.27 (~WE), U9.10 (~WR), U10.23 (~WR), U24.15 (B3)
IRQ0: U10.10 (OUT0), U43.11 (D0)
IRQ2: J7.4 (IRQ2), J20.4 (IRQ2), J21.4 (IRQ2), J22.4 (IRQ2)
IRQ3: J7.25 (IRQ3), J20.25 (IRQ3), J21.25 (IRQ3), J22.25 (IRQ3), U43.14 (D3)
IRQ4: J7.24 (IRQ4), J20.24 (IRQ4), J21.24 (IRQ4), J22.24 (IRQ4), U43.3 (D4)
IRQ5: J7.23 (IRQ5), J20.23 (IRQ5), J21.23 (IRQ5), J22.23 (IRQ5), U43.4 (D5)
IRQ6: J7.22 (IRQ6), J20.22 (IRQ6), J21.22 (IRQ6), J22.22 (IRQ6), U43.5 (D6)
IRQ7: J7.21 (IRQ7), J20.21 (IRQ7), J21.21 (IRQ7), J22.21 (IRQ7), U43.6 (D7)
IRQ8: R7.1, U8.5 (~IRQ), U41.11 (D0)
IRQ10: J7.65 (IRQ10), J20.65 (IRQ10), J21.65 (IRQ10), J22.65 (IRQ10), U41.13 (D2)
IRQ11: J7.66 (IRQ11), J20.66 (IRQ11), J21.66 (IRQ11), J22.66 (IRQ11), U41.14 (D3)
IRQ12: J7.67 (IRQ12), J20.67 (IRQ12), J21.67 (IRQ12), J22.67 (IRQ12), U41.3 (D4)
IRQ14: J7.69 (IRQ14), J20.69 (IRQ14), J21.69 (IRQ14), J22.69 (IRQ14), U41.5 (D6)
IRQ15: J7.68 (IRQ15), J20.68 (IRQ15), J21.68 (IRQ15), J22.68 (IRQ15), U41.6 (D7)
ISA_00: J1.7, J7.40 (DB0), J20.40 (DB0), J21.40 (DB0), J22.40 (DB0), U6.13 (D0), U8.11 (D0), U9.12 (D0), U10.8 (D0), U34.47 (1A0)
ISA_01: J1.8, J7.39 (DB1), J20.39 (DB1), J21.39 (DB1), J22.39 (DB1), U6.14 (D1), U8.12 (D1), U9.13 (D1), U10.7 (D1), U34.46 (1A1)
ISA_02: J1.9, J7.38 (DB2), J20.38 (DB2), J21.38 (DB2), J22.38 (DB2), U6.15 (D2), U8.13 (D2), U9.14 (D2), U10.6 (D2), U34.44 (1A2)
ISA_03: J1.10, J7.37 (DB3), J20.37 (DB3), J21.37 (DB3), J22.37 (DB3), U6.17 (D3), U8.15 (D3), U9.15 (D3), U10.5 (D3), U34.43 (1A3)
ISA_04: J1.11, J7.36 (DB4), J20.36 (DB4), J21.36 (DB4), J22.36 (DB4), U6.18 (D4), U8.16 (D4), U9.16 (D4), U10.4 (D4), U34.41 (1A4)
ISA_05: J1.12, J7.35 (DB5), J20.35 (DB5), J21.35 (DB5), J22.35 (DB5), U6.19 (D5), U8.17 (D5), U9.17 (D5), U10.3 (D5), U34.40 (1A5)
ISA_06: J1.13, J7.34 (DB6), J20.34 (DB6), J21.34 (DB6), J22.34 (DB6), U6.20 (D6), U8.18 (D6), U9.18 (D6), U10.2 (D6), U34.38 (1A6)
ISA_07: J1.14, J7.33 (DB7), J20.33 (DB7), J21.33 (DB7), J22.33 (DB7), U6.21 (D7), U8.19 (D7), U9.19 (D7), U10.1 (D7), U34.37 (1A7)
ISA_08: J7.91 (D8), J20.91 (D8), J21.91 (D8), J22.91 (D8), U34.36 (2A0)
ISA_09: J7.92 (D9), J20.92 (D9), J21.92 (D9), J22.92 (D9), U34.35 (2A1)
ISA_10: J7.93 (D10), J20.93 (D10), J21.93 (D10), J22.93 (D10), U34.33 (2A2)
ISA_11: J7.94 (D11), J20.94 (D11), J21.94 (D11), J22.94 (D11), U34.32 (2A3)
ISA_12: J7.95 (D12), J20.95 (D12), J21.95 (D12), J22.95 (D12), U34.30 (2A4)
ISA_13: J7.96 (D13), J20.96 (D13), J21.96 (D13), J22.96 (D13), U34.29 (2A5)
ISA_14: J7.97 (D14), J20.97 (D14), J21.97 (D14), J22.97 (D14), U34.27 (2A6)
ISA_15: J7.98 (D15), J20.98 (D15), J21.98 (D15), J22.98 (D15), U34.26 (2A7)
ISA_A00: J7.62 (BA00), J20.62 (BA00), J21.62 (BA00), J22.62 (BA00), U21.47 (1A0)
ISA_A01: J7.61 (BA01), J20.61 (BA01), J21.61 (BA01), J22.61 (BA01), U21.46 (1A1)
ISA_A02: J7.60 (BA02), J20.60 (BA02), J21.60 (BA02), J22.60 (BA02), U21.44 (1A2)
ISA_A03: J7.59 (BA03), J20.59 (BA03), J21.59 (BA03), J22.59 (BA03), U21.43 (1A3)
ISA_A04: J7.58 (BA04), J20.58 (BA04), J21.58 (BA04), J22.58 (BA04), U21.41 (1A4)
ISA_A05: J7.57 (BA05), J20.57 (BA05), J21.57 (BA05), J22.57 (BA05), U21.40 (1A5)
ISA_A06: J7.56 (BA06), J20.56 (BA06), J21.56 (BA06), J22.56 (BA06), U21.38 (1A6)
ISA_A07: J7.55 (BA07), J20.55 (BA07), J21.55 (BA07), J22.55 (BA07), U21.37 (1A7)
ISA_A08: J7.54 (BA08), J20.54 (BA08), J21.54 (BA08), J22.54 (BA08), U21.36 (2A0)
ISA_A09: J7.53 (BA09), J20.53 (BA09), J21.53 (BA09), J22.53 (BA09), U21.35 (2A1)
ISA_A10: J7.52 (BA10), J20.52 (BA10), J21.52 (BA10), J22.52 (BA10), U21.33 (2A2)
ISA_A11: J7.51 (BA11), J20.51 (BA11), J21.51 (BA11), J22.51 (BA11), U21.32 (2A3)
ISA_A12: J7.50 (BA12), J20.50 (BA12), J21.50 (BA12), J22.50 (BA12), U21.30 (2A4)
ISA_A13: J7.49 (BA13), J20.49 (BA13), J21.49 (BA13), J22.49 (BA13), U21.29 (2A5)
ISA_A14: J7.48 (BA14), J20.48 (BA14), J21.48 (BA14), J22.48 (BA14), U21.27 (2A6)
ISA_A15: J7.47 (BA15), J20.47 (BA15), J21.47 (BA15), J22.47 (BA15), U21.26 (2A7)
ISA_A16: J7.46 (BA16), J20.46 (BA16), J21.46 (BA16), J22.46 (BA16), U35.47 (1A0)
ISA_A17: J7.45 (BA17), J7.88 (LA17), J20.45 (BA17), J20.88 (LA17), J21.45 (BA17), J21.88 (LA17), J22.45 (BA17), J22.88 (LA17), U35.46 (1A1)
ISA_A18: J7.44 (BA18), J7.87 (LA18), J20.44 (BA18), J20.87 (LA18), J21.44 (BA18), J21.87 (LA18), J22.44 (BA18), J22.87 (LA18), U35.44 (1A2)
ISA_A19: J7.43 (BA19), J7.86 (LA19), J20.43 (BA19), J20.86 (LA19), J21.43 (BA19), J21.86 (LA19), J22.43 (BA19), J22.86 (LA19), U35.43 (1A3)
ISA_A20: J7.85 (LA20), J20.85 (LA20), J21.85 (LA20), J22.85 (LA20), U35.41 (1A4)
ISA_A21: J7.84 (LA21), J20.84 (LA21), J21.84 (LA21), J22.84 (LA21), U35.40 (1A5)
ISA_A22: J7.83 (LA22), J20.83 (LA22), J21.83 (LA22), J22.83 (LA22), U35.38 (1A6)
ISA_A23: J7.82 (LA23), J20.82 (LA23), J21.82 (LA23), J22.82 (LA23), U35.37 (1A7)
ISA_CLK: J7.20 (CLK), J20.20 (CLK), J21.20 (CLK), J22.20 (CLK), U11.141 (IOT_219)
ISA_High_en: U12.16 (IOL_10B), U34.25 (2~OE)
ISA_Low_en: U12.15 (IOL_10A), U34.48 (1~OE)
ISA_RESET: J7.2 (RESET), J20.2 (RESET), J21.2 (RESET), J22.2 (RESET), J34.2
ISA_WAIT: U11.43 (IOB_71), U12.48 (IOB_80)
ISA_dir: U12.12 (IOL_8B), U34.1 (1DIR), U34.24 (2DIR)
KBD_A20: J3.2, U9.22 (A20)
KEN: J10.6, U25.F15 (KEN)
LOCK: J10.10, U25.N15 (LOCK), U27.4 (A2)
MASTER16: J7.79 (MASTER), J20.79 (MASTER), J21.79 (MASTER), J22.79 (MASTER), U46.11 (D0)
MCLK0: J28.1, U11.60 (IOB_95)
MCLK2: J28.3, U10.9 (CLK0), U10.15 (CLK1), U10.18 (CLK2)
MEMCS16: J7.63 (~MEMCS16), J20.63 (~MEMCS16), J21.63 (~MEMCS16), J22.63 (~MEMCS16), U27.8 (A6)
MEMR: J7.89 (~MEMR), J20.89 (~MEMR), J21.89 (~MEMR), J22.89 (~MEMR), U1.37 (~OE), U2.37 (~OE), U3.37 (~OE), U4.37 (~OE), U6.24 (OE), U24.18 (B0)
MEMW: J2.3, J7.90 (~MEMW), J20.90 (~MEMW), J21.90 (~MEMW), J22.90 (~MEMW), U1.15 (~WE), U2.15 (~WE), U3.15 (~WE), U4.15 (~WE), U24.17 (B1)
M/IO: J33.3, U23.8 (A6), U25.N16 (M/IO)
NOWS: J7.8 (UNUSED), J20.8 (UNUSED), J21.8 (UNUSED), J22.8 (UNUSED), U27.6 (A4)
unnamed: BT1.1 (+), U8.25 (Vbat)
unnamed: D1.1 (K), U12.108 (VPP_2V5)
unnamed: D2.1 (K), R41.1
unnamed: D3.1 (K), U11.108 (VPP_2V5)
unnamed: D4.1 (K), R46.1
unnamed: D5.2 (A), J26.8 (PWR_OK)
unnamed: D5.1 (K), R48.1
unnamed: J1.15, R1.1
unnamed: J2.1, R2.2
unnamed: J2.2, U6.31 (WE)
unnamed: J3.3, R9.2
unnamed: J5.4, U45.3
unnamed: J8.2, U25.J1 (Vcc)
unnamed: J9.3, R15.1
unnamed: J9.5, R13.1
unnamed: J11.2, U25.S4 (VOLDET)
unnamed: J13.1, R27.2
unnamed: J13.3, R28.1
unnamed: J14.1, R29.1
unnamed: J14.2, U25.C10 (SRESET)
unnamed: J19.3 (D+), R47.1
unnamed: J19.2 (D-), R51.1
unnamed: J7.32 (IO), J20.32 (IO), J21.32 (IO), J22.32 (IO)
unnamed: J7.30 (OSC), J20.30 (OSC), J21.30 (OSC), J22.30 (OSC)
unnamed: J24.1, R57.2
unnamed: J24.2, U25.R17 (CLKMUL)
unnamed: J24.3, R58.2
unnamed: J25.2, J26.16 (PS_ON#)
unnamed: J27.1, R54.1
unnamed: J29.1, U25.B14 (TMS)
unnamed: J29.2, U25.A14 (TDI)
unnamed: J29.3, U25.B16 (TDO)
unnamed: J29.4, U25.A3 (TCK)
unnamed: R50.2, R71.1
unnamed: U1.8 (~CE), U5.11
unnamed: U2.8 (~CE), U5.8
unnamed: U3.8 (~CE), U5.6
unnamed: U4.8 (~CE), U5.3
unnamed: R4.2, U8.1 (Vout)
unnamed: U8.2 (X1), Y2.2
unnamed: U8.3 (X2), Y2.1
unnamed: R68.1, U8.24 (~KS)
unnamed: R3.2, U8.4 (~RST)
unnamed: U7.5, U9.37 (KBCO)
unnamed: U7.9, U9.38 (KBDO)
unnamed: U7.3, U9.23 (P22/MSDO)
unnamed: U7.1, U9.24 (P23/MSCO)
unnamed: C5.2, U9.2 (xtal_1), Y1.1
unnamed: C8.2, U9.3 (xtal_2), Y1.2
unnamed: R5.1, U9.34 (~KBD-INH)
unnamed: R6.1, U10.14 (G1)
unnamed: R8.1, U10.16 (G2)
unnamed: U10.17 (OUT2), U45.2
unnamed: C58.2, C59.2, U11.53 (GNDPLL0), U11.127 (GNDPLL1)
unnamed: C58.1, C59.1, R42.2, U11.54 (VCCPLL0), U11.126 (VCCPLL1)
unnamed: C51.2, C52.2, U12.53 (GNDPLL0), U12.127 (GNDPLL1)
unnamed: C51.1, C52.1, R37.2, U12.54 (VCCPLL0), U12.126 (VCCPLL1)
unnamed: R10.2, U13.1 (A->B)
unnamed: R12.2, U14.1 (A->B)
unnamed: R14.2, U15.1 (A->B)
unnamed: R16.2, U16.1 (A->B)
unnamed: R62.2, U21.1 (1DIR)
unnamed: R66.1, U21.48 (1~OE)
unnamed: R63.2, U21.24 (2DIR)
unnamed: R67.1, U21.25 (2~OE)
unnamed: R36.1, U22.2 (1G)
unnamed: U22.1 (CLKIN), X1.8 (OUT)
unnamed: R59.2, U23.1 (A->B)
unnamed: R34.2, U23.19 (CE)
unnamed: R61.2, U24.1 (A->B)
unnamed: R33.2, U24.19 (CE)
unnamed: R25.2, U25.N3 (DP0)
unnamed: R24.2, U25.F1 (DP1)
unnamed: R23.2, U25.H3 (DP2)
unnamed: R22.2, U25.A5 (DP3)
unnamed: R17.2, U25.C14 (FERR)
unnamed: R11.2, U25.A15 (IGNNE)
unnamed: R26.1, U25.B15 (NMI)
unnamed: R60.2, U27.1 (A->B)
unnamed: R52.2, U27.19 (CE)
unnamed: R69.1, U28.3 (EN)
unnamed: R70.1, U29.3 (EN)
unnamed: R32.2, U35.1 (1DIR)
unnamed: R65.1, U35.48 (1~OE)
unnamed: R31.2, U35.24 (2DIR)
unnamed: R64.1, U35.25 (2~OE)
unnamed: R49.2, R50.1, U40.1 (ADJ)
unnamed: U41.10 (DS), U43.9 (Q7)
unnamed: U43.10 (DS), U46.9 (Q7)
unnamed: R35.2, X1.1 (Tri-State)
PCD: J10.3, U25.J17 (PCD)
PCHK: J10.4, U25.Q17 (PCHK)
PIC0_en: U11.45 (IOB_73), U12.52 (IOB_82_GBIN4)
PIT_en: U10.21 (~CS), U11.49 (IOB_81_GBIN5)
PWT: J10.9, U25.L15 (PWT)
RDY: J33.13, U11.22 (IOL_14B), U25.F16 (RDY)
REFRESH: J7.19 (~REFRESH), J20.19 (~REFRESH), J21.19 (~REFRESH), J22.19 (~REFRESH), U10.13 (OUT1), U11.64 (IOB_104_CBSEL1), U12.129 (IOT_198_GBIN0)
RESET: J34.1, U7.11, U9.4 (reset), U11.39 (IOB_61), U12.73 (IOR_109)
S1: U12.10 (IOL_5B), U33.30 (~S0)
S2: U12.9 (IOL_5A), U33.45 (~S2)
SA0: U12.91 (IOR_139), U33.165 (SA0)
SA1: U12.90 (IOR_138), U33.166 (SA1)
SA2: U12.88 (IOR_137), U33.167 (SA2)
SBHE: J7.81 (SBHE), J20.81 (SBHE), J21.81 (SBHE), J22.81 (SBHE)
SCL: J28.4, U11.63 (IOB_103_CBSEL0)
SDA: J28.5, U11.62 (IOB_102)
SDRAM_HIGH_BUS: U11.56 (IOB_94), U12.11 (IOL_8A)
SDRAM_HWORD: U12.37 (IOB_56), U38.1 (OE), U39.1 (OE), U48.1 (OE), U49.1 (OE)
SDRAM_LATCH: U12.38 (IOB_57), U38.11 (LE), U39.11 (LE), U48.11 (LE), U49.11 (LE)
SDRAM_SCL: U12.97 (IOR_147), U33.83 (SCL)
SDRAM_SDA: U12.96 (IOR_146), U33.82 (SDA)
SHIFT_CLK_EN: U12.79 (IOR_115), U41.15 (~CE), U43.15 (~CE), U46.15 (~CE)
SHIFT_EN: U41.1 (~PL), U43.1 (~PL), U46.1 (~PL)
SMEMR: J7.12 (~SMEMR), J20.12 (~SMEMR), J21.12 (~SMEMR), J22.12 (~SMEMR), U24.14 (B4)
SMEMW: J7.11 (~SMEMW), J20.11 (~SMEMW), J21.11 (~SMEMW), J22.11 (~SMEMW), U24.13 (B5)
SMIACT: J10.2, U25.C12 (SMIACT)
SPI_DI: J36.2, U11.67 (IOB_105_SDO), U36.5 (SI/IO0)
SPI_DI2: J35.2, U12.67 (IOB_105_SDO), U32.5 (SI/IO0)
SPI_DO: J36.3, U11.68 (IOB_106_SDI), U36.2 (SO/IO1)
SPI_DO2: J35.3, U12.68 (IOB_106_SDI), U32.2 (SO/IO1)
SPI_SCK: J36.4, R43.2, U11.70 (IOB_107_SCK), U36.6 (CLK)
SPI_SCK2: J35.4, R38.2, U12.70 (IOB_107_SCK), U32.6 (CLK)
SPI_SS: J36.1, R45.1, U11.71 (IOB_108_SS), U36.1 (~CS)
SPI_SS2: J35.1, R40.1, U12.71 (IOB_108_SS), U32.1 (~CS)
STPCLK: J9.10, R21.2, U25.G15 (STPCLK)
TC: J7.27 (TC), J20.27 (TC), J21.27 (TC), J22.27 (TC), U46.3 (D4)
TE0: J33.5, U11.1 (IOL_2A), U17.19 (CE)
TE1: J33.6, U11.2 (IOL_2B), U18.19 (CE)
TE2: J33.7, U11.3 (IOL_3A), U19.19 (CE)
TE3: J33.8, U11.4 (IOL_3B), U20.19 (CE)
UNUSED0: J23.5, U11.139 (IOT_217), U12.61 (IOB_96)
UNUSED1: J23.4, U12.60 (IOB_95)
UNUSED2: J23.1, U12.56 (IOB_94)
UP: J9.9, U25.C11 (UP)
USBD+: R47.2, U11.23 (IOL_17A)
USBD-: R51.2, U11.24 (IOL_17B)
WTWB: J13.2, U25.B13 (WB/WT)
W/R: J33.1, U17.1 (A->B), U18.1 (A->B), U19.1 (A->B), U20.1 (A->B), U23.6 (A4), U25.N17 (W/R)
cpu_vcc: C21.2, C22.2, C23.2, C24.2, C25.2, C26.2, C27.2, C28.2, C29.1, C30.1, C31.1, C32.1, C33.1, C34.1, C35.1, C36.1, C37.1, C38.1, J9.14, J10.14, J11.1, J12.2, R22.1, R23.1, R24.1, R25.1, R28.2, R57.1, U25.B7 (Vcc), U25.B9 (Vcc), U25.B11 (Vcc), U25.C4 (Vcc), U25.C5 (Vcc), U25.E2 (Vcc), U25.E16 (Vcc), U25.G2 (Vcc), U25.G16 (Vcc), U25.H16 (Vcc), U25.K2 (Vcc), U25.K16 (Vcc), U25.L16 (Vcc), U25.M2 (Vcc), U25.M16 (Vcc), U25.P16 (Vcc), U25.R3 (Vcc), U25.R6 (Vcc), U25.R8 (Vcc), U25.R9 (Vcc), U25.R10 (Vcc), U25.R11 (Vcc), U25.R14 (Vcc)
cpu_vcc_in: C92.1, C93.1, J12.3, R49.1, U40.2 (VO)
dram0_CKE: U12.76 (IOR_112), U33.128 (CKE0)
dram0_en: U11.38 (IOB_57), U12.95 (IOR_144)
dram_A00: U11.119 (IOT_178), U33.33 (A0)
dram_A01: U11.120 (IOT_179), U33.117 (A1)
dram_A02: U11.121 (IOT_181), U33.34 (A2)
dram_A03: U11.122 (IOT_190), U33.118 (A3)
dram_A04: U11.124 (IOT_191), U33.35 (A4)
dram_A05: U11.125 (IOT_192), U33.119 (A5)
dram_A06: U11.128 (IOT_197_GBIN1), U33.36 (A6)
dram_A07: U11.129 (IOT_198_GBIN0), U33.120 (A7)
dram_A08: U11.130 (IOT_206), U33.37 (A8)
dram_A09: U11.134 (IOT_212), U33.121 (A9)
dram_A10: U11.135 (IOT_213), U33.38 (A10)
dram_A11: U11.136 (IOT_214), U33.123 (A11)
dram_A12: U11.137 (IOT_215), U33.126 (A12)
dram_WE: U11.47 (IOB_79), U12.55 (IOB_91), U33.27 (~WE)
isabus_en: J33.14, U11.33 (IOL_25A), U12.47 (IOB_79)
kbd_clk: C9.2, J4.5, U7.6, U9.1 (KBCI)
kbd_data: C10.2, J4.1, U7.8, U9.27 (P10/KBDI)
kbd_en: U9.6 (~CS), U11.44 (IOB_72)
lcd_en: J1.6, U11.7 (IOL_4A)
ms_clk: C6.2, J6.5, U7.2, U9.39 (KBDI/MSCI)
ms_data: C7.2, J6.1, U7.4, U9.28 (P11/MSDI)
rom_en: J33.15, U6.22 (CE), U11.55 (IOB_91)
rtc_en: U8.20 (~CE), U11.48 (IOB_80)
sram_en: J33.9, U5.1, U5.4, U5.9, U5.12, U11.8 (IOL_4B)
x00: U11.18 (IOL_12B), U12.34 (IOL_25B), U34.2 (1B0)
x01: U11.17 (IOL_12A), U12.33 (IOL_25A), U34.3 (1B1)
x02: U11.16 (IOL_10B), U12.32 (IOL_24B), U34.5 (1B2)
x03: U11.15 (IOL_10A), U12.31 (IOL_24A), U34.6 (1B3)
x04: U11.12 (IOL_8B), U12.29 (IOL_23B), U34.8 (1B4)
x05: U11.11 (IOL_8A), U12.28 (IOL_23A), U34.9 (1B5)
x06: U11.10 (IOL_5B), U12.26 (IOL_18B), U34.11 (1B6)
x07: U11.9 (IOL_5A), U12.25 (IOL_18A), U34.12 (1B7)
x08: U12.24 (IOL_17B), U34.13 (2B0)
x09: U12.23 (IOL_17A), U34.14 (2B1)
x10: U12.22 (IOL_14B), U34.16 (2B2)
x11: U12.21 (IOL_14A_GBIN6), U34.17 (2B3)
x12: U12.20 (IOL_13B_GBIN7), U34.19 (2B4)
x13: U12.19 (IOL_13A), U34.20 (2B5)
x14: U12.18 (IOL_12B), U34.22 (2B6)
x15: U12.17 (IOL_12A), U34.23 (2B7)
~CAS: U12.42 (IOB_64), U33.115 (~RAS)
~RAS: U12.43 (IOB_71), U33.111 (~CAS)
~RESET: J34.3, U7.10, U25.C16 (RESET)
